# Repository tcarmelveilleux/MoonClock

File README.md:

# MoonClock

A unique analog and digital clock that displays the current phase of the moon and the number of hours of darkness available for astronomical observation in the evening.

## Features

* **Analog Moon Phase Dial:** Visually represents the current lunar phase using a modified micro-ammeter.
* **Analog Darkness Hours Dial:** Indicates the duration of darkness in the evening after astronomical twilight, crucial for stargazing, using a modified micro-ammeter.
* **Digital Time Display:** A dot matrix display shows the current time.
* **Real-Time Clock (RTC):** Keeps accurate time, even when not powered.
* **3D Printed Frame:** The clock's frame is a single piece designed to be 3D printed.
* **Powered by Raspberry Pi RP2040:** Uses the WaveShare RP2040-Zero module for its easy to use form-factor.
* **CircuitPython Implementation:** The project is coded in CircuitPython, making it accessible and easy to modify.
* **Custom Astronomical Calculations:** Employs the `tcv_astro` module, specifically developed for this project using algorithms from astronomical literature (primarily "Astronomical Algorithms" by Jean Meeus).

## Hardware

* Raspberry Pi RP2040-based module (e.g., Waveshare RP2040-Zero)
* Real-Time Clock (RTC) module based on DS3231 (Rev 1) and MCP7940 (Rev 2)
* Dot matrix display based on MAX7219
* Modified micro-ammeters analog dials and associated DAC and amplifiers.
* 3D-printed frame (PETG)

## Software

* CircuitPython firmware for the Raspberry Pi RP2040
  * Custom build with Double Precision floating-point arithmetic enabled.
* `tcv_astro` CircuitPython module (containing astronomical calculation functions).
  * This module was written custom for this project to have very little dependencies.
* Libraries for controlling the RTC, dot matrix display, and the modified micro-ammeters (a lot of Adafruit CircuitPython libraries)

## `tcv_astro` Module

This project features a custom-built CircuitPython module, `tcv_astro`, which handles the necessary astronomical calculations. It implements algorithms described in Jean Meeus's "Astronomical Algorithms.":
  *  Meeus, J. (1991). Astronomical algorithms (1st ed.). Willmann-Bell.

This module computes:
* The current phase of the moon.
* Sunrise, sunset, moonset and moonrise times to determine the duration of evening darkness.

## Getting Started

Instructions for building and setting up your own MoonClock will be provided in future updates. This will include details on:

* 3D printing the frame.
* Modifying and wiring the micro-ammeters and other electronic components.
* Installing CircuitPython and necessary libraries.
* Uploading the code to the RP2040-Zero.

## Contributing

Contributions to this project are welcome! If you have ideas for improvements, bug fixes, or new features, please feel free to open an issue or submit a pull request.

## License

MIT license, see the LICENSE file.

## Acknowledgements

* The Raspberry Pi Foundation for the RP2040 microcontroller.
* The Afafruit CircuitPython community for their excellent libraries and support.
* Jean Meeus for his invaluable and authoritastive "Astronomical Algorithms" book

---

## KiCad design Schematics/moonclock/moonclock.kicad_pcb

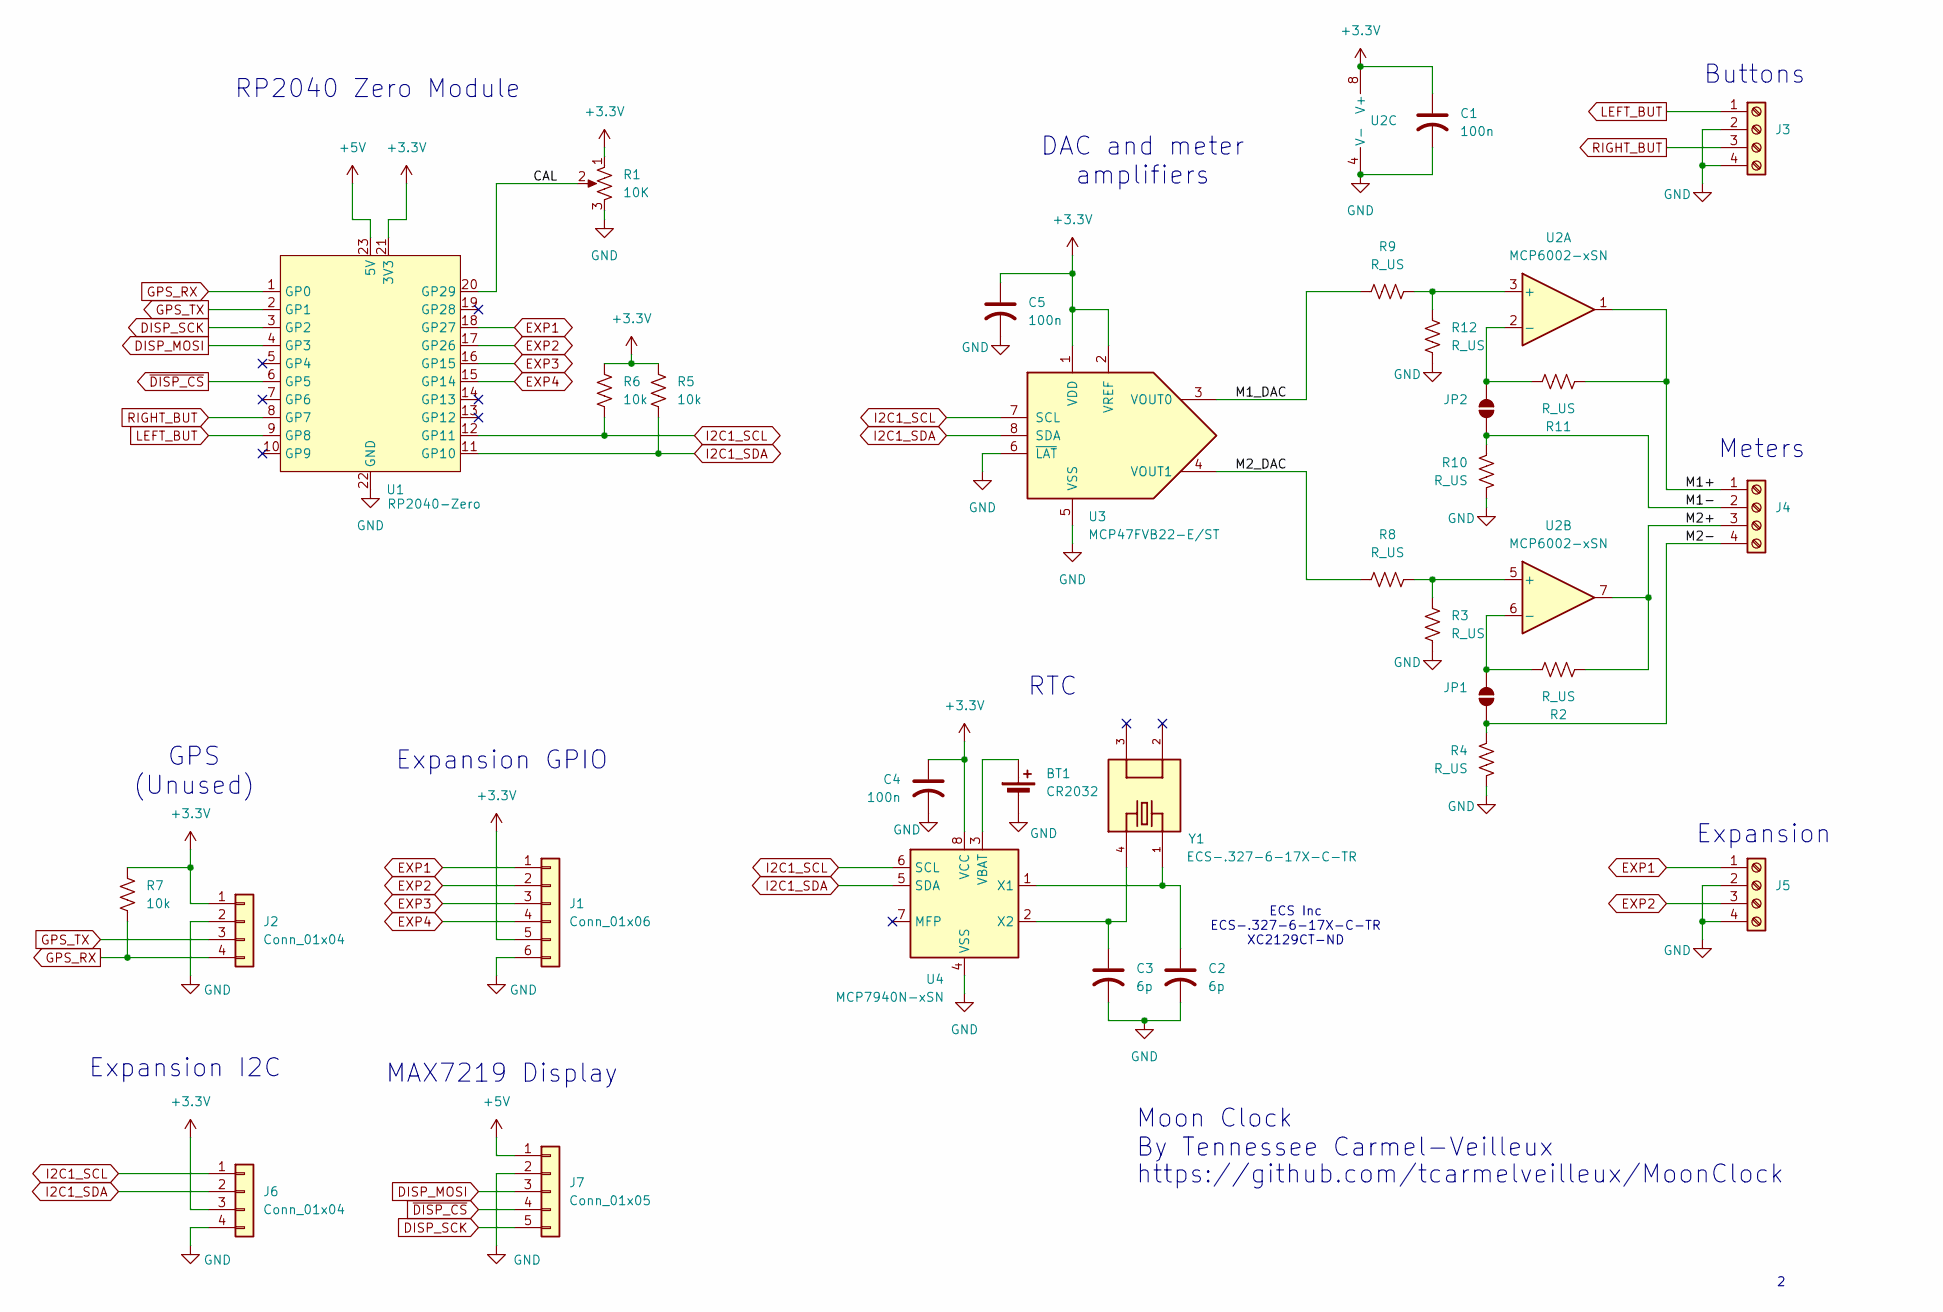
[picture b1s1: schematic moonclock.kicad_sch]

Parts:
BT1: CR2032; BAT_BS-7
C1, C4, C5: 100n; C_0805_2012Metric_Pad1.18x1.45mm_HandSolder
C2, C3: 6p; C_0603_1608Metric_Pad1.08x0.95mm_HandSolder
J1: Conn_01x06; PinHeader_1x06_P2.54mm_Vertical
J2, J6: Conn_01x04; PinHeader_1x04_P2.54mm_Vertical
J3, J4, J5: Screw_Terminal_01x04; TerminalBlock_Phoenix_MKDS-1,5-4-5.08_1x04_P5.08mm_Horizont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
J7: Conn_01x05; PinHeader_1x05_P2.54mm_Vertical
JP1, JP2: SolderJumper_2_Open; SolderJumper-2_P1.3mm_Open_RoundedPad1.0x1.5mm
R1: 10K; Potentiometer_Bourns_3296W_Vertical
R2, R3, R4, R8, R9, R10, R11, R12: R_US; R_0805_2012Metric_Pad1.20x1.40mm_HandSolder
R5, R6, R7: 10k; R_0805_2012Metric_Pad1.20x1.40mm_HandSolder
U1: RP2040-Zero
U2: MCP6002-xSN; SOIC-8_3.9x4.9mm_P1.27mm
U3: MCP47FVB22-E/ST; TSSOP-8_4.4x3mm_P0.65mm
U4: MCP7940N-xSN; SOIC-8_3.9x4.9mm_P1.27mm
Y1: ECS-.327-6-17X-C-TR; XTAL_ECS-.327-6-17X-C-TR; PARTREV 2016

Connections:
+3.3V: C1.1, C4.1, C5.1, J1.5, J2.1, J6.3, R1.1, R5.1, R6.1, R7.1, U1.21 (3V3), U2.8 (V+), U3.1 (VDD), U3.2 (VREF), U4.8 (VCC)
+5V: J7.1, U1.23 (5V)
/CAL: R1.2, U1.20 (GP29)
/M1+: J4.1, R11.2, U2.1
/M1-: J4.2, JP2.1 (A), R10.1
/M1_DAC: R9.1, U3.3 (VOUT0)
/M2+: J4.3, R2.2, U2.7
/M2-: J4.4, JP1.1 (A), R4.1
/M2_DAC: R8.1, U3.4 (VOUT1)
DISP_MOSI: J7.3, U1.4 (GP3)
DISP_SCK: J7.5, U1.3 (GP2)
EXP1: J1.1, J5.1, U1.18 (GP27)
EXP2: J1.2, J5.3, U1.17 (GP26)
EXP3: J1.3, U1.16 (GP15)
EXP4: J1.4, U1.15 (GP14)
GND: BT1.2 (-), C1.2, C2.2, C3.2, C4.2, C5.2, J1.6, J2.2, J3.2, J3.4, J5.2, J5.4, J6.4, J7.2, R1.3, R3.2, R4.2, R10.2, R12.2, U1.22 (GND), U2.4 (V-), U3.5 (VSS), U3.6 (~LAT), U4.4 (VSS)
GPS_RX: J2.4, R7.2, U1.1 (GP0)
GPS_TX: J2.3, U1.2 (GP1)
I2C1_SCL: J6.1, R6.2, U1.12 (GP11), U3.7 (SCL), U4.6 (SCL)
I2C1_SDA: J6.2, R5.2, U1.11 (GP10), U3.8 (SDA), U4.5 (SDA)
LEFT_BUT: J3.1, U1.9 (GP8)
unnamed: BT1.1 (+), U4.3 (VBAT)
unnamed: JP1.2 (B), R2.1, U2.6 (-)
unnamed: JP2.2 (B), R11.1, U2.2 (-)
unnamed: R9.2, R12.1, U2.3 (+)
unnamed: R3.1, R8.2, U2.5 (+)
unnamed: C2.1, U4.1 (X1), Y1.1
unnamed: C3.1, U4.2 (X2), Y1.4
RIGHT_BUT: J3.3, U1.8 (GP7)
~DISP_CS: J7.4, U1.6 (GP5)

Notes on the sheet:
DAC and meter amplifiers
https://github.com/tcarmelveilleux/MoonClock
Buttons
MAX7219 Display
ECS Inc ECS-.327-6-17X-C-TR XC2129CT-ND
Expansion GPIO
Moon Clock By Tennessee Carmel-Veilleux
RP2040 Zero Module
Expansion
RTC
GPS (Unused)
Meters
Expansion I2C

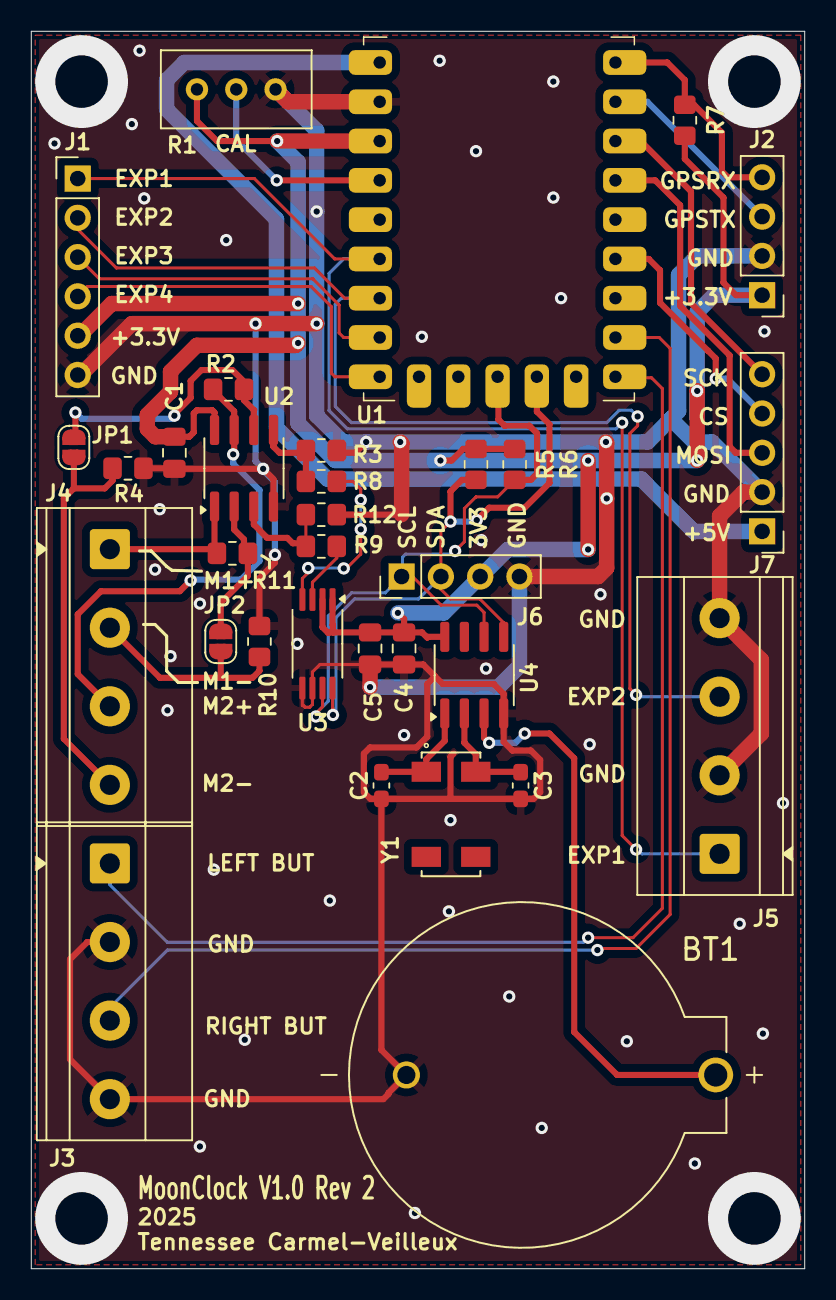
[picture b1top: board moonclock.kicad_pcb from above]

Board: 2 copper layers, 50.0 x 80.0 mm, 32 parts (0 on the bottom side), 30 nets.

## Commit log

2025-04-13 Add normalized moon age to tcv_astro
2025-04-13 Added screen management framework
2025-04-19 Sun and moon times work, date screen works
2025-04-20 Full clock works!
2025-04-20 Minor fixes
2025-04-26 Added schematic and PCB
2025-05-04 Try to fix daily crash
2025-05-04 Minor PCB updates
2025-05-11 Start on rev 2 design
2025-05-11 Fix 3.3V label
2025-05-15 minor change
2025-05-18 Rev 1 PCB working, fixed refdes C4/R8, fixed moon phase cal
2025-05-18 Finished Rev2 pre-gerber
2025-05-18 Remove garbage RP2040 zero footprint from GH after redo
2025-05-18 Moved gerbers from Rev1
2025-05-18 Fix footprint for U1 and corner vias
2025-05-19 Rev2 hardware ready
2025-05-19 Add datasheets for rev 2
2025-05-19 Added README.md
2025-05-19 Add AUTHOR/SUBJECT variables to project
2025-05-19 Add title block to schematic and update rp2040 library location
2025-05-19 Fix rp2040 library association
2025-05-19 Schematic cosmetic improvements and PDF plot
2025-05-19 Schematic cosmetic improvements
2025-05-19 Add rev 1 schematic to master
